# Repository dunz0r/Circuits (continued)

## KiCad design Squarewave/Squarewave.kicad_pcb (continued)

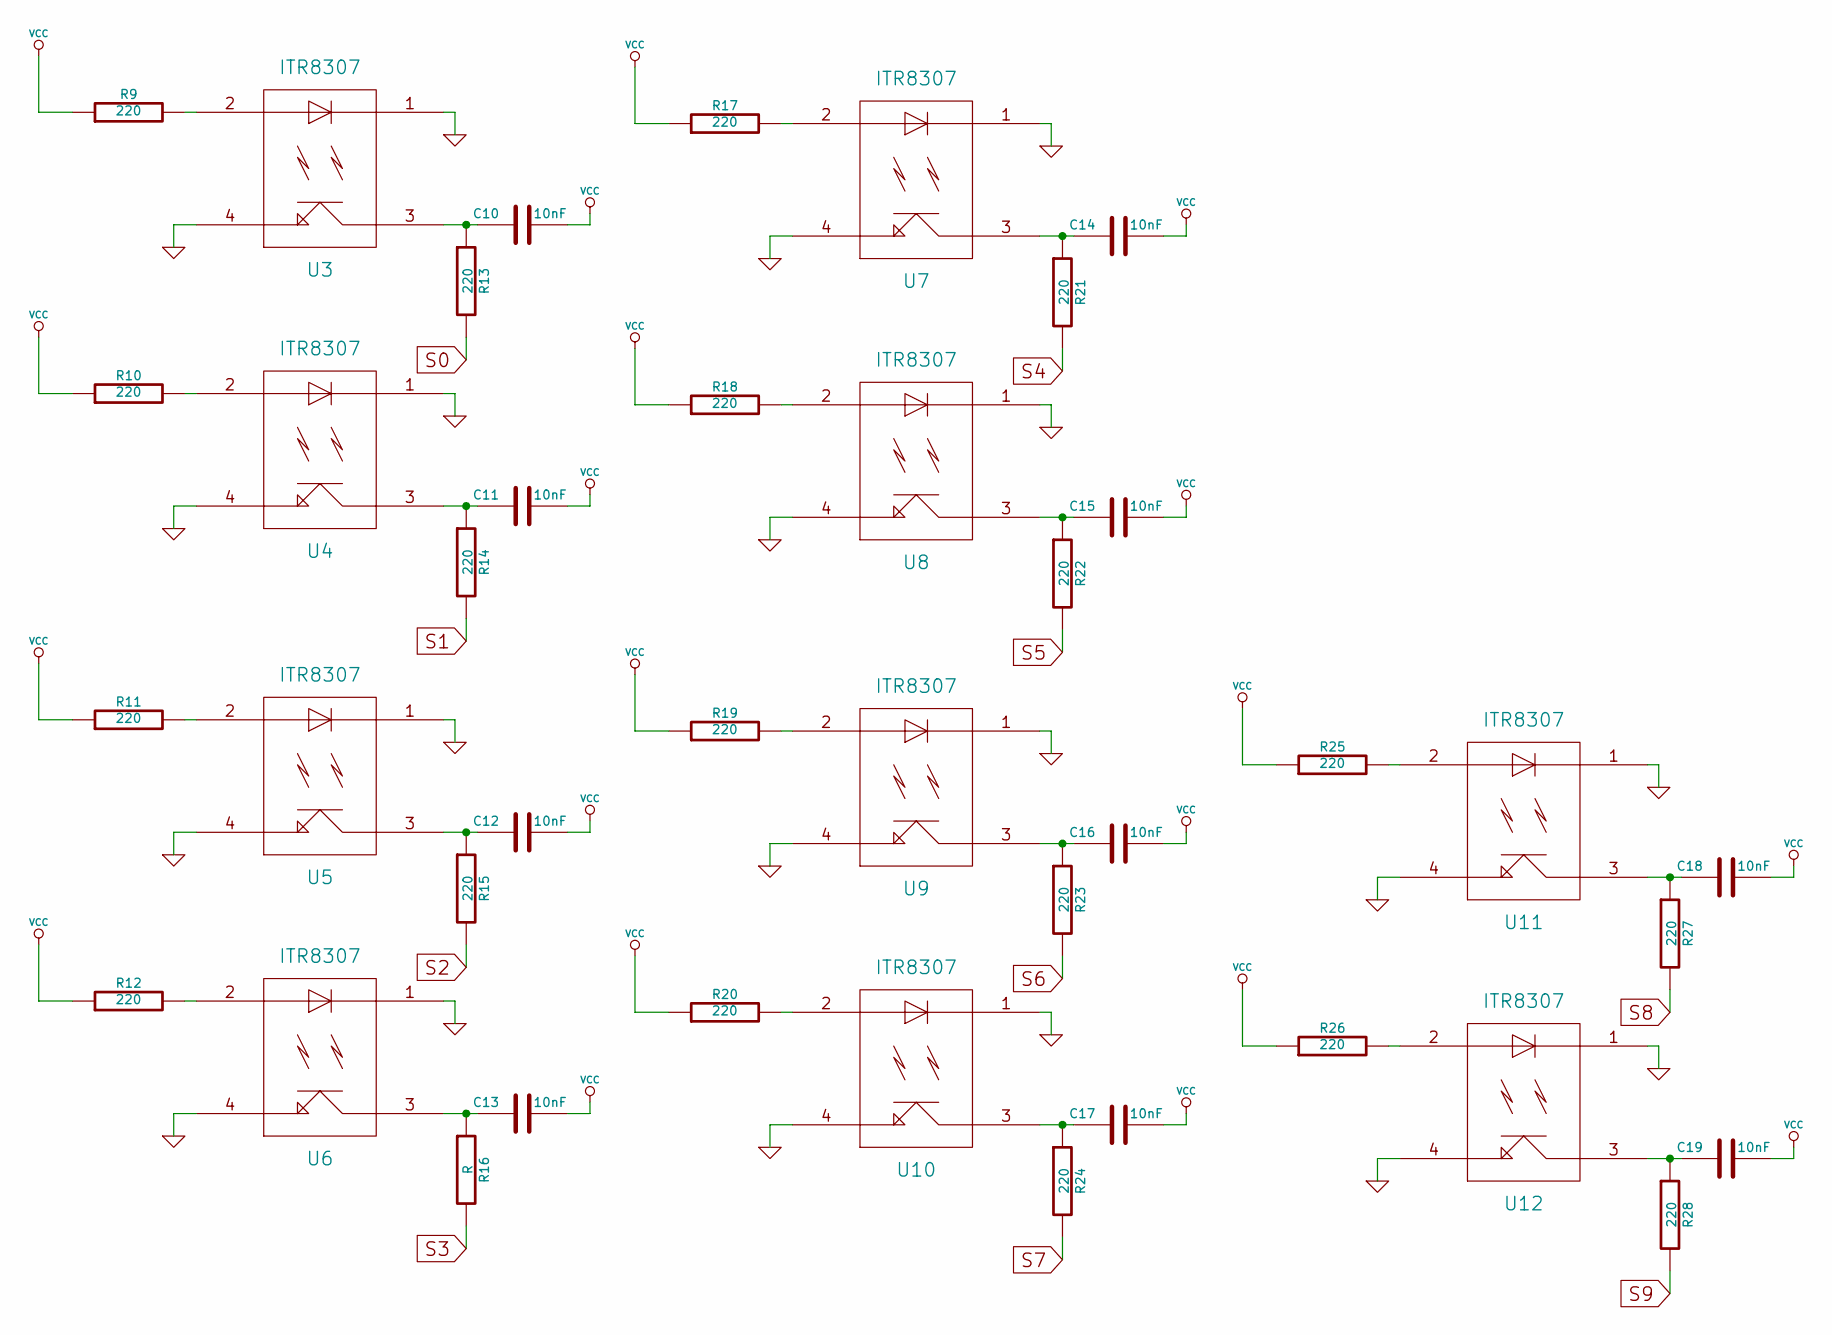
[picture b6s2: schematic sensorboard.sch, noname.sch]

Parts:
C10, C11, C12, C13, C14, C15, C16, C17, C18, C19: 10nF
R9, R10, R11, R12, R13, R14, R15, R17, R18, R19, R20, R21, R22, R23, R24, R25, R26, R27, R28: 220
R16: R
U3, U4, U5, U6, U7, U8, U9, U10, U11, U12: ITR8307

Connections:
GND: U3.1, U3.4, U4.1, U4.4, U5.1, U5.4, U6.1, U6.4, U7.1, U7.4, U8.1, U8.4, U9.1, U9.4, U10.1, U10.4, U11.1, U11.4, U12.1, U12.4; also elsewhere on the board
unnamed: R17.2, U7.2
unnamed: C14.1, R21.1, U7.3
unnamed: R18.2, U8.2
unnamed: R9.2, U3.2
unnamed: R10.2, U4.2
unnamed: C15.1, R22.1, U8.3
unnamed: R26.2, U12.2
unnamed: R25.2, U11.2
unnamed: C19.1, R28.1, U12.3
unnamed: C18.1, R27.1, U11.3
unnamed: R11.2, U5.2
unnamed: R12.2, U6.2
unnamed: R20.2, U10.2
unnamed: C17.1, R24.1, U10.3
unnamed: C13.1, R16.1, U6.3
unnamed: C12.1, R15.1, U5.3
unnamed: C11.1, R14.1, U4.3
unnamed: R19.2, U9.2
unnamed: C10.1, R13.1, U3.3
unnamed: C16.1, R23.1, U9.3
S0: R13.2; also elsewhere on the board
S1: R14.2; also elsewhere on the board
S2: R15.2; also elsewhere on the board
S3: R16.2; also elsewhere on the board
S4: R21.2; also elsewhere on the board
S5: R22.2; also elsewhere on the board
S6: R23.2; also elsewhere on the board
S7: R24.2; also elsewhere on the board
S8: R27.2; also elsewhere on the board
S9: R28.2; also elsewhere on the board
VCC: C10.2, C11.2, C12.2, C13.2, C14.2, C15.2, C16.2, C17.2, C18.2, C19.2, R9.1, R10.1, R11.1, R12.1, R17.1, R18.1, R19.1, R20.1, R25.1, R26.1; also elsewhere on the board

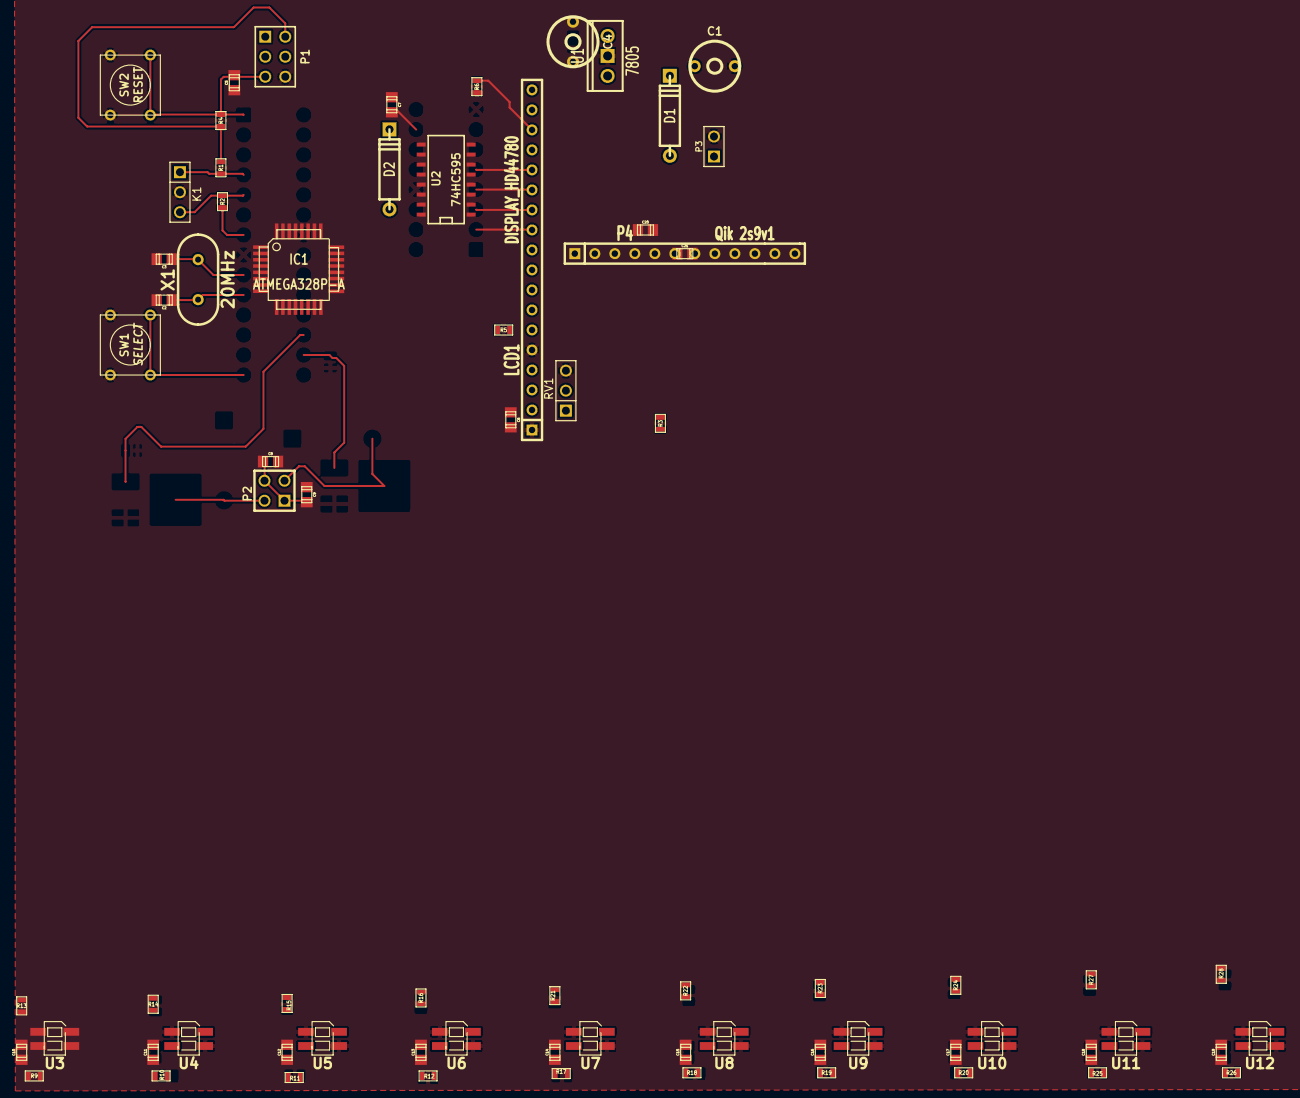
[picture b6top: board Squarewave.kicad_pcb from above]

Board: 2 copper layers, 72 parts (0 on the bottom side), 60 nets.

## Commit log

2013-06-07 Some stuff added
2013-06-07 More files added, some eaglefiles too :O
2013-06-07 Edited README
2014-02-11 Added Amplifier and visualizer
2014-03-23 The timerbox added
2014-08-11 Added some libs and some new circuits
